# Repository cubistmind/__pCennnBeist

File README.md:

# ___being_pCB-eist
welcome to tHe world of my own custom pcB's

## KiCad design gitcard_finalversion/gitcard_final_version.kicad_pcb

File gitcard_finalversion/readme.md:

# PCB gitcard -stuckatprototype

A custom PCB based "emniii😞😞" card that lets you play a version of Flappy Bird

## Project Structure
The project consists of
1. Firmware
2. Hardware
3. Mechanical
4. Scripts

These are structured into their own files. I could have used submodules, but decided against it.

### 1. Firmware
This lives on the ESP32
soon the necessary firmware files will be included here 
### 2. Hardware

#### Schematic
PDF schematic included for your viewing pleasure.
#### PCBs
All the gerber files you'd need to send to a fab house.
#### Kicad
All the files you'd need to expand and work on this further. If you'd like.

### 3. Mechanical

#### Enclosure
All the step files you need to make one of these. Extrusion printer works well for this part.

### 4. Scripts

soon it will be added🥲

#### Requirements
A bunch of pip packages

## What the project could use
1. Cleanup, but thats true for almost anything out there
2. A proper graphics library -- Adafruit, or even LVGL 
3. Scripts that would show stock data. anyone? 

## If you take it further
Let me know if you ever make one of these, I'd love to see it. Seriously, that'd be exciting and inspiring to keep making my projects open source!

## Known issues
1. Switch requires to be shorted due to power consumption at run time
2. GPIO 1 as is does not allow the device to wake up from sleep
3. The LEDs seem to be pulling a lot power even when ESP32 is in deep sleep mode
## Special Thanks
Thanks to Michael Angerer for his open sourced `esp32_ble_ota` project. I used it to get BLE running in this project. His blog post and github repo are a great resource. Check it out. https://github.com/micha

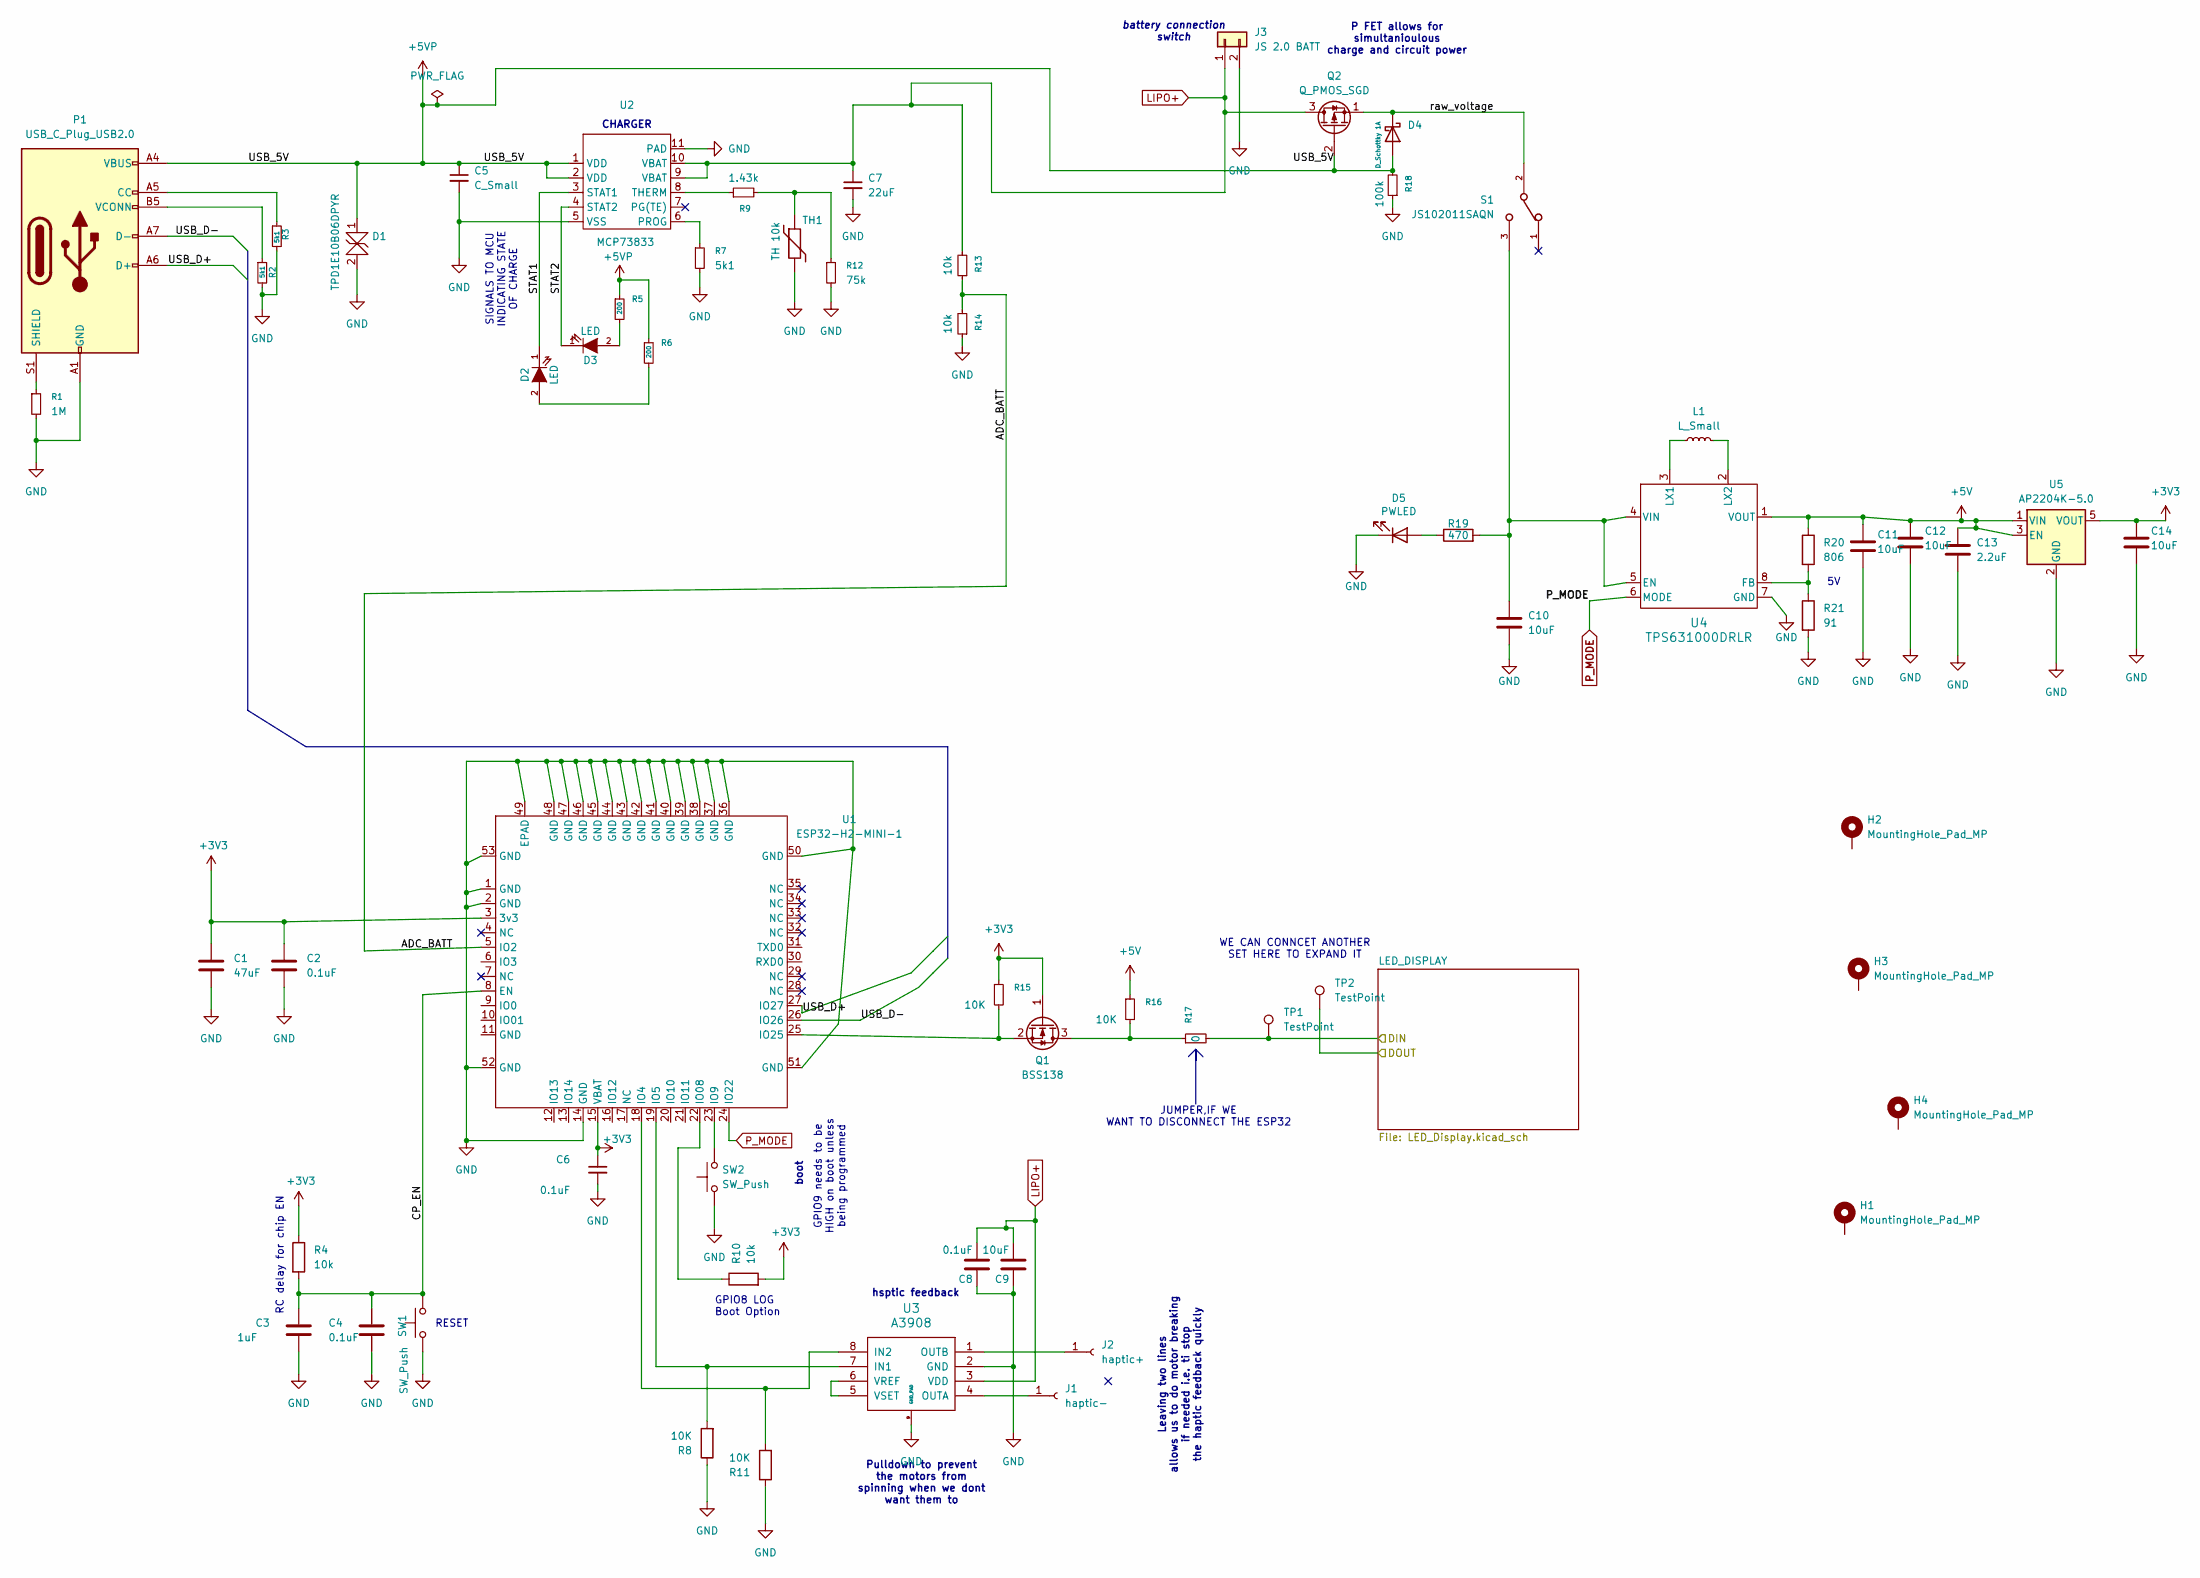
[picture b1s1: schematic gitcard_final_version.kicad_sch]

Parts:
C1: 47uF; C_0603_1608Metric
C2, C4, C6, C8: 0.1uF; C_0603_1608Metric
C3: 1uF; C_0603_1608Metric
C5: C_Small; C_0603_1608Metric
C7: 22uF; C_0603_1608Metric
C9, C10, C11, C12, C14: 10uF; C_0603_1608Metric
C13: 2.2uF; C_0603_1608Metric
D1: TPD1E10B06DPYR; D_SOD-523
D2, D3: LED; D_0603_1608Metric
D4: D_Schottky 1A; D_SMA
D5: PWLED; D_0603_1608Metric
H1, H2, H3, H4: MountingHole_Pad_MP; MountingHole_3.5mm_Pad_TopBottom
J1: haptic-; SolderWirePad_1x01_SMD_3x6mm
J2: haptic+; SolderWirePad_1x01_SMD_3x6mm
J3: JS 2.0 BATT; JST_PH_B2B-PH-SM4-TB_1x02-1MP_P2.00mm_Vertical
L1: L_Small; L_0805_2012Metric
P1: USB_C_Plug_USB2.0; USB_C_Plug_Molex_105444
Q1: BSS138; SOT-23
Q2: Q_PMOS_SGD; SOT-89-3
R1: 1M; L_0805_2012Metric
R2, R3, R7: 5k1; R_0603_1608Metric
R4, R10, R13, R14: 10k; R_0603_1608Metric
R5, R6: 200; R_0603_1608Metric
R8, R11, R15, R16: 10K; R_0603_1608Metric
R9: 1.43k; R_0603_1608Metric
R12: 75k; R_0603_1608Metric
R17: 0; R_0603_1608Metric
R18: 100k; R_0603_1608Metric
R19: 470; R_0603_1608Metric
R20: 806; R_0603_1608Metric
R21: 91; R_0603_1608Metric
S1: JS102011SAQN; SW_SPDT_CK_JS102011SAQN
SW1, SW2: SW_Push; SW_Push_1P1T_NO_CK_KSC7xxJ
TH1: TH 10k; R_0603_1608Metric
TP1, TP2: TestPoint; TestPoint_Pad_1.5x1.5mm
U1: ESP32-H2-MINI-1; MODULE_ESP32-H2-MINI-1-H2_1
U2: MCP73833; SON50P300X300X100-11N
U3: A3908
U4: TPS631000DRLR; TPS631000DRLR_TEX
U5: AP2204K-5.0; SOT-23-5

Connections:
+3V3: C1.1, C2.1, C6.1, C14.1, Q1.1 (G), R4.1, R10.2, R15.1, U1.3 (3v3), U1.15 (VBAT), U5.5 (VOUT)
+5V: C11.1, C12.1, C13.1, R16.1, R20.1, U4.1 (VOUT), U5.1 (VIN), U5.3 (EN); also elsewhere on the board
+5VP: C5.1, D1.1, D4.2 (A), P1.A4 (VBUS), P1.A9 (VBUS), P1.B4 (VBUS), P1.B9 (VBUS), Q2.2 (G), R5.1, R6.1, R18.2, U2.1 (VDD), U2.2 (VDD)
/ADC_BATT: R13.1, R14.2, U1.5 (IO2)
/CP_EN: C3.1, C4.1, R4.2, SW1.2, U1.8 (EN)
/DIN: R17.2, TP1.1 (1_1)
/DOUT: TP2.1 (1_1)
/STAT1: D2.1 (K), U2.3 (STAT1)
/STAT2: D3.1 (K), U2.4 (STAT2)
/USB_D+: P1.A6 (D+), U1.27 (IO27)
/USB_D-: P1.A7 (D-), U1.26 (IO26)
/raw_voltage: D4.1 (K), Q2.1 (S), S1.2
GND: C1.2, C2.2, C3.2, C4.2, C5.2, C6.2, C7.2, C8.1, C9.1, C10.2, C11.2, C12.2, C13.2, C14.2, D1.2, D5.1 (K), J3.2, P1.A1 (GND), P1.A12 (GND), P1.B1 (GND), P1.B12 (GND), R1.2, R2.2, R3.2, R7.2, R8.1, R11.1, R12.2, R14.1, R18.1, R21.2, SW1.1, SW2.1, TH1.2, U1.1 (GND), U1.2 (GND), U1.14 (GND), U1.36 (GND), U1.37 (GND), U1.38 (GND), U1.39 (GND), U1.40 (GND), U1.41 (GND), U1.42 (GND), U1.43 (GND), U1.44 (GND), U1.45 (GND), U1.46 (GND), U1.47 (GND), U1.48 (GND), U1.49 (EPAD), U1.50 (GND), U1.51 (GND), U1.52 (GND), U1.53 (GND), U2.5 (VSS), U2.11 (PAD), U3.2 (GND), U3.9 (GND_PAD), U4.7 (GND), U5.2 (GND); also elsewhere on the board
LIPO+: C7.1, C8.2, C9.2, J3.1, Q2.3 (D), R13.2, U2.9 (VBAT), U2.10 (VBAT), U3.3 (VDD)
unnamed: D2.2 (A), R6.2
unnamed: D3.2 (A), R5.2
unnamed: D5.2 (A), R19.1
unnamed: J1.1 (Pin_1_1), U3.4 (OUTA)
unnamed: J2.1 (Pin_1_1), U3.1 (OUTB)
unnamed: P1.A5 (CC), R3.1
unnamed: P1.S1 (SHIELD), R1.1
unnamed: P1.B5 (VCONN), R2.1
unnamed: Q1.3 (D), R16.2, R17.1
unnamed: Q1.2 (S), R15.2, U1.25 (IO25)
unnamed: R9.2, R12.1, TH1.1
unnamed: R11.2, U1.18 (IO4), U3.8 (IN2)
unnamed: R8.2, U1.19 (IO5), U3.7 (IN1)
unnamed: R10.1, U1.22 (IO08)
unnamed: SW2.2, U1.23 (IO9)
unnamed: R7.1, U2.6 (PROG)
unnamed: R9.1, U2.8 (THERM)
unnamed: U3.5 (VSET), U3.6 (VREF)
unnamed: C10.1, R19.2, S1.3, U4.4 (VIN), U4.5 (EN)
unnamed: R20.2, R21.1, U4.8 (FB)
unnamed: L1.1, U4.3 (LX1)
unnamed: L1.2, U4.2 (LX2)
P_MODE: U1.24 (IO22), U4.6 (MODE)

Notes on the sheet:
battery connection switch
Pulldown to prevent the motors from spinning when we dont want them to
boot
CHARGER
RESET
SIGNALS TO MCU INDICATING STATE OF CHARGE
Leaving two lines allows us to do motor breaking if needed i.e. ti stop the haptic feedback quickly
JUMPER,IF WE WANT TO DISCONNECT THE ESP32
GPIO9 needs to be HIGH on boot unless being programmed
GPIO8 LOG Boot Option
WE CAN CONNCET ANOTHER SET HERE TO EXPAND IT
P FET allows for simultanioulous charge and circuit power
RC delay for chip EN
hsptic feedback

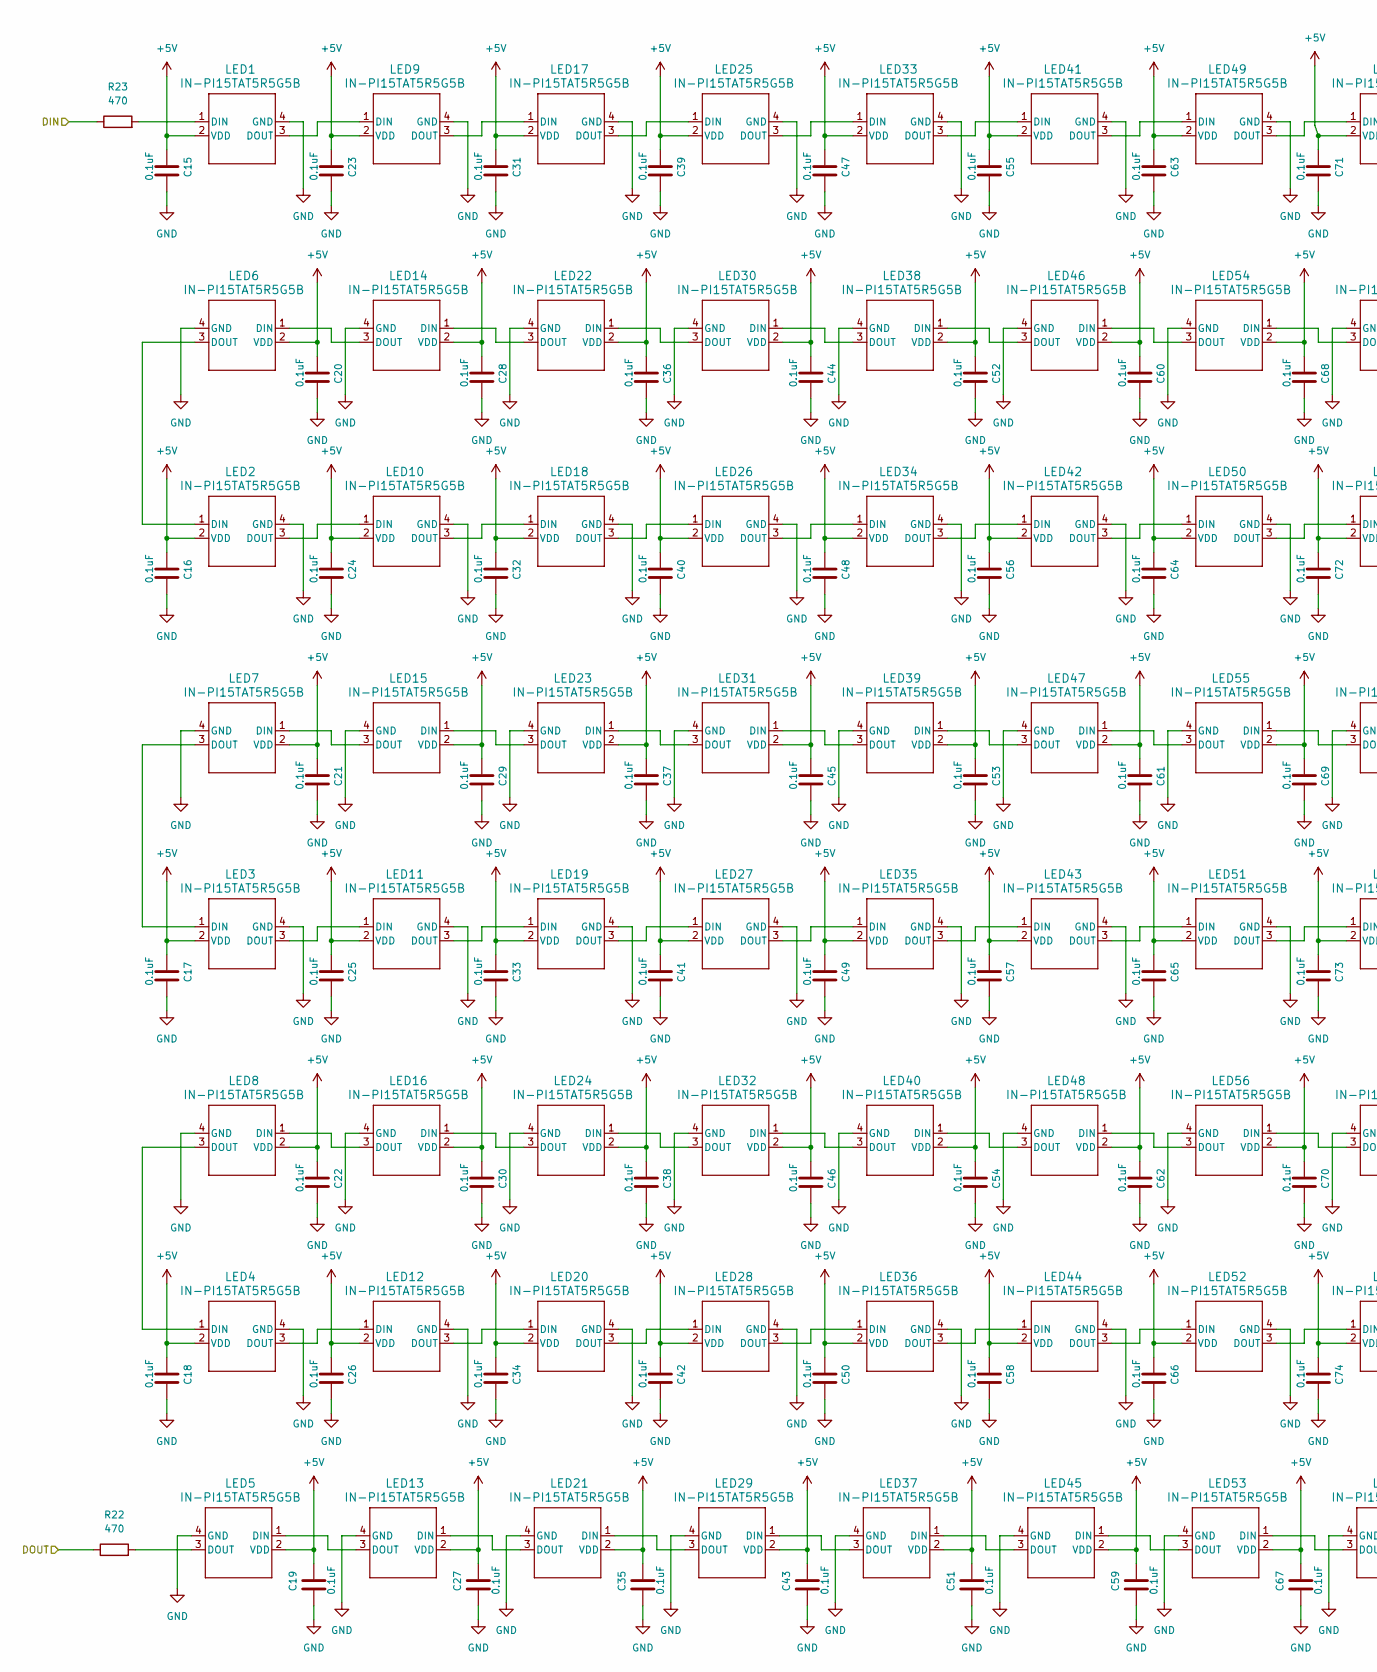
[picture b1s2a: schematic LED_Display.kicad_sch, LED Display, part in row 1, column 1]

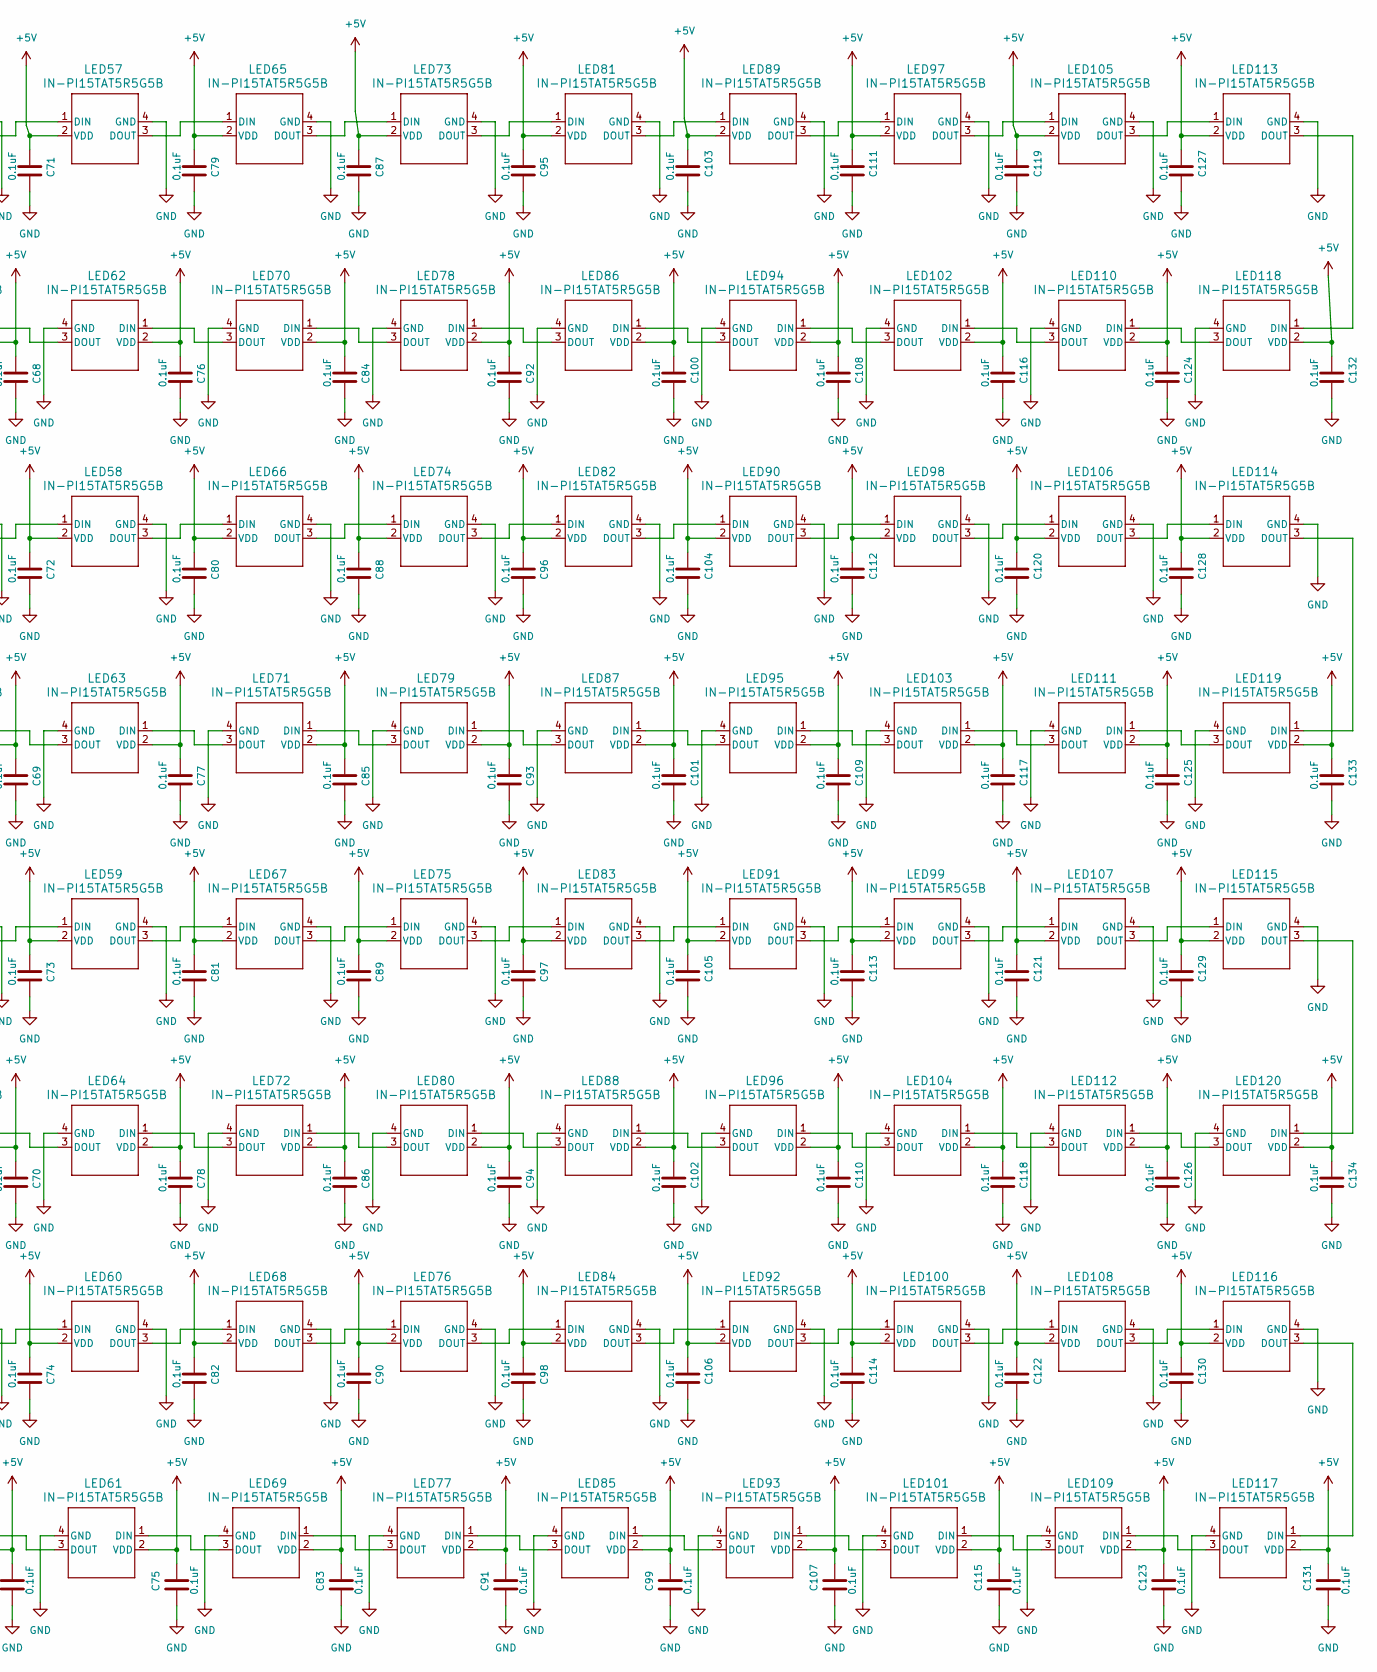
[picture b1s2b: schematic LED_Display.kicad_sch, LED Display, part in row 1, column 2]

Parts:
C15, C16, C17, C18, C19, C20, C21, C22, C23, C24, C25, C26, C27, C28, C29, C30, C31, C32, C33, C34, C35, C36, C37, C38, C39, C40, C41, C42, C43, C44, C45, C46, C47, C48, C49, C50, C51, C52, C53, C54, C55, C56, C57, C58, C59, C60, C61, C62, C63, C64, C65, C66, C67, C68, C69, C70, C71, C72, C73, C74, C75, C76, C77, C78, C79, C80, C81, C82, C83, C84, C85, C86, C87, C88, C89, C90, C91, C92, C93, C94, C95, C96, C97, C98, C99, C100, C101, C102, C103, C104, C105, C106, C107, C108, C109, C110, C111, C112, C113, C114, C115, C116, C117, C118, C119, C120, C121, C122, C123, C124, C125, C126, C127, C128, C129, C130, C131, C132, C133, C134: 0.1uF; C_0603_1608Metric
LED1, LED2, LED3, LED4, LED5, LED6, LED7, LED8, LED9, LED10, LED11, LED12, LED13, LED14, LED15, LED16, LED17, LED18, LED19, LED20, LED21, LED22, LED23, LED24, LED25, LED26, LED27, LED28, LED29, LED30, LED31, LED32, LED33, LED34, LED35, LED36, LED37, LED38, LED39, LED40, LED41, LED42, LED43, LED44, LED45, LED46, LED47, LED48, LED49, LED50, LED51, LED52, LED53, LED54, LED55, LED56, LED57, LED58, LED59, LED60, LED61, LED62, LED63, LED64, LED65, LED66, LED67, LED68, LED69, LED70, LED71, LED72, LED73, LED74, LED75, LED76, LED77, LED78, LED79, LED80, LED81, LED82, LED83, LED84, LED85, LED86, LED87, LED88, LED89, LED90, LED91, LED92, LED93, LED94, LED95, LED96, LED97, LED98, LED99, LED100, LED101, LED102, LED103, LED104, LED105, LED106, LED107, LED108, LED109, LED110, LED111, LED112, LED113, LED114, LED115, LED116, LED117, LED118, LED119, LED120: IN-PI15TAT5R5G5B; IN-PI15_INL
R22, R23: 470; R_0603_1608Metric

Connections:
+5V: C15.1, C16.1, C17.1, C18.1, C19.1, C20.1, C21.1, C22.1, C23.1, C24.1, C25.1, C26.1, C27.1, C28.1, C29.1, C30.1, C31.1, C32.1, C33.1, C34.1, C35.1, C36.1, C37.1, C38.1, C39.1, C40.1, C41.1, C42.1, C43.1, C44.1, C45.1, C46.1, C47.1, C48.1, C49.1, C50.1, C51.1, C52.1, C53.1, C54.1, C55.1, C56.1, C57.1, C58.1, C59.1, C60.1, C61.1, C62.1, C63.1, C64.1, C65.1, C66.1, C67.1, C68.1, C69.1, C70.1, C71.1, C72.1, C73.1, C74.1, C75.1, C76.1, C77.1, C78.1, C79.1, C80.1, C81.1, C82.1, C83.1, C84.1, C85.1, C86.1, C87.1, C88.1, C89.1, C90.1, C91.1, C92.1, C93.1, C94.1, C95.1, C96.1, C97.1, C98.1, C99.1, C100.1, C101.1, C102.1, C103.1, C104.1, C105.1, C106.1, C107.1, C108.1, C109.1, C110.1, C111.1, C112.1, C113.1, C114.1, C115.1, C116.1, C117.1, C118.1, C119.1, C120.1, C121.1, C122.1, C123.1, C124.1, C125.1, C126.1, C127.1, C128.1, C129.1, C130.1, C131.1, C132.1, C133.1, C134.1, LED1.2 (VDD), LED2.2 (VDD), LED3.2 (VDD), LED4.2 (VDD), LED5.2 (VDD), LED6.2 (VDD), LED7.2 (VDD), LED8.2 (VDD), LED9.2 (VDD), LED10.2 (VDD), LED11.2 (VDD), LED12.2 (VDD), LED13.2 (VDD), LED14.2 (VDD), LED15.2 (VDD), LED16.2 (VDD), LED17.2 (VDD), LED18.2 (VDD), LED19.2 (VDD), LED20.2 (VDD), LED21.2 (VDD), LED22.2 (VDD), LED23.2 (VDD), LED24.2 (VDD), LED25.2 (VDD), LED26.2 (VDD), LED27.2 (VDD), LED28.2 (VDD), LED29.2 (VDD), LED30.2 (VDD), LED31.2 (VDD), LED32.2 (VDD), LED33.2 (VDD), LED34.2 (VDD), LED35.2 (VDD), LED36.2 (VDD), LED37.2 (VDD), LED38.2 (VDD), LED39.2 (VDD), LED40.2 (VDD), LED41.2 (VDD), LED42.2 (VDD), LED43.2 (VDD), LED44.2 (VDD), LED45.2 (VDD), LED46.2 (VDD), LED47.2 (VDD)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; also elsewhere on the board
/LED_DISPLAY/DIN: R23.1
/LED_DISPLAY/DOUT: R22.1
GND: C15.2, C16.2, C17.2, C18.2, C19.2, C20.2, C21.2, C22.2, C23.2, C24.2, C25.2, C26.2, C27.2, C28.2, C29.2, C30.2, C31.2, C32.2, C33.2, C34.2, C35.2, C36.2, C37.2, C38.2, C39.2, C40.2, C41.2, C42.2, C43.2, C44.2, C45.2, C46.2, C47.2, C48.2, C49.2, C50.2, C51.2, C52.2, C53.2, C54.2, C55.2, C56.2, C57.2, C58.2, C59.2, C60.2, C61.2, C62.2, C63.2, C64.2, C65.2, C66.2, C67.2, C68.2, C69.2, C70.2, C71.2, C72.2, C73.2, C74.2, C75.2, C76.2, C77.2, C78.2, C79.2, C80.2, C81.2, C82.2, C83.2, C84.2, C85.2, C86.2, C87.2, C88.2, C89.2, C90.2, C91.2, C92.2, C93.2, C94.2, C95.2, C96.2, C97.2, C98.2, C99.2, C100.2, C101.2, C102.2, C103.2, C104.2, C105.2, C106.2, C107.2, C108.2, C109.2, C110.2, C111.2, C112.2, C113.2, C114.2, C115.2, C116.2, C117.2, C118.2, C119.2, C120.2, C121.2, C122.2, C123.2, C124.2, C125.2, C126.2, C127.2, C128.2, C129.2, C130.2, C131.2, C132.2, C133.2, C134.2, LED1.4 (GND), LED2.4 (GND), LED3.4 (GND), LED4.4 (GND), LED5.4 (GND), LED6.4 (GND), LED7.4 (GND), LED8.4 (GND), LED9.4 (GND), LED10.4 (GND), LED11.4 (GND), LED12.4 (GND), LED13.4 (GND), LED14.4 (GND), LED15.4 (GND), LED16.4 (GND), LED17.4 (GND), LED18.4 (GND), LED19.4 (GND), LED20.4 (GND), LED21.4 (GND), LED22.4 (GND), LED23.4 (GND), LED24.4 (GND), LED25.4 (GND), LED26.4 (GND), LED27.4 (GND), LED28.4 (GND), LED29.4 (GND), LED30.4 (GND), LED31.4 (GND), LED32.4 (GND), LED33.4 (GND), LED34.4 (GND), LED35.4 (GND), LED36.4 (GND), LED37.4 (GND), LED38.4 (GND), LED39.4 (GND), LED40.4 (GND), LED41.4 (GND), LED42.4 (GND), LED43.4 (GND), LED44.4 (GND), LED45.4 (GND), LED46.4 (GND), LED47.4 (GND)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; also elsewhere on the board
unnamed: LED1.1 (DIN), R23.2
unnamed: LED1.3 (DOUT), LED9.1 (DIN)
unnamed: LED2.1 (DIN), LED6.3 (DOUT)
unnamed: LED3.1 (DIN), LED7.3 (DOUT)
unnamed: LED4.1 (DIN), LED8.3 (DOUT)
unnamed: LED5.3 (DOUT), R22.2
unnamed: LED2.3 (DOUT), LED10.1 (DIN)
unnamed: LED10.3 (DOUT), LED18.1 (DIN)
unnamed: LED3.3 (DOUT), LED11.1 (DIN)
unnamed: LED11.3 (DOUT), LED19.1 (DIN)
unnamed: LED4.3 (DOUT), LED12.1 (DIN)
unnamed: LED12.3 (DOUT), LED20.1 (DIN)
unnamed: LED13.1 (DIN), LED21.3 (DOUT)
unnamed: LED5.1 (DIN), LED13.3 (DOUT)
unnamed: LED14.1 (DIN), LED22.3 (DOUT)
unnamed: LED6.1 (DIN), LED14.3 (DOUT)
unnamed: LED15.1 (DIN), LED23.3 (DOUT)
unnamed: LED7.1 (DIN), LED15.3 (DOUT)
unnamed: LED16.1 (DIN), LED24.3 (DOUT)
unnamed: LED8.1 (DIN), LED16.3 (DOUT)
unnamed: LED9.3 (DOUT), LED17.1 (DIN)
unnamed: LED17.3 (DOUT), LED25.1 (DIN)
unnamed: LED18.3 (DOUT), LED26.1 (DIN)
unnamed: LED19.3 (DOUT), LED27.1 (DIN)
unnamed: LED20.3 (DOUT), LED28.1 (DIN)
unnamed: LED21.1 (DIN), LED29.3 (DOUT)
unnamed: LED22.1 (DIN), LED30.3 (DOUT)
unnamed: LED23.1 (DIN), LED31.3 (DOUT)
unnamed: LED24.1 (DIN), LED32.3 (DOUT)
unnamed: LED25.3 (DOUT), LED33.1 (DIN)
unnamed: LED26.3 (DOUT), LED34.1 (DIN)
unnamed: LED27.3 (DOUT), LED35.1 (DIN)
unnamed: LED28.3 (DOUT), LED36.1 (DIN)
unnamed: LED29.1 (DIN), LED37.3 (DOUT)
unnamed: LED30.1 (DIN), LED38.3 (DOUT)
unnamed: LED31.1 (DIN), LED39.3 (DOUT)
unnamed: LED32.1 (DIN), LED40.3 (DOUT)
unnamed: LED33.3 (DOUT), LED41.1 (DIN)
unnamed: LED34.3 (DOUT), LED42.1 (DIN)
unnamed: LED35.3 (DOUT), LED43.1 (DIN)
unnamed: LED36.3 (DOUT), LED44.1 (DIN)
unnamed: LED37.1 (DIN), LED45.3 (DOUT)
unnamed: LED38.1 (DIN), LED46.3 (DOUT)
unnamed: LED39.1 (DIN), LED47.3 (DOUT)
unnamed: LED40.1 (DIN), LED48.3 (DOUT)
unnamed: LED41.3 (DOUT), LED49.1 (DIN)
unnamed: LED42.3 (DOUT), LED50.1 (DIN)
unnamed: LED43.3 (DOUT), LED51.1 (DIN)
unnamed: LED44.3 (DOUT), LED52.1 (DIN)
unnamed: LED45.1 (DIN), LED53.3 (DOUT)
unnamed: LED46.1 (DIN), LED54.3 (DOUT)
unnamed: LED47.1 (DIN), LED55.3 (DOUT)
unnamed: LED48.1 (DIN), LED56.3 (DOUT)
unnamed: LED49.3 (DOUT), LED57.1 (DIN)
unnamed: LED50.3 (DOUT), LED58.1 (DIN)
unnamed: LED51.3 (DOUT), LED59.1 (DIN)
unnamed: LED52.3 (DOUT), LED60.1 (DIN)
unnamed: LED53.1 (DIN), LED61.3 (DOUT)
unnamed: LED54.1 (DIN), LED62.3 (DOUT)
unnamed: LED55.1 (DIN), LED63.3 (DOUT)
unnamed: LED56.1 (DIN), LED64.3 (DOUT)
unnamed: LED57.3 (DOUT), LED65.1 (DIN)
unnamed: LED58.3 (DOUT), LED66.1 (DIN)
unnamed: LED59.3 (DOUT), LED67.1 (DIN)
unnamed: LED60.3 (DOUT), LED68.1 (DIN)
unnamed: LED61.1 (DIN), LED69.3 (DOUT)
unnamed: LED62.1 (DIN), LED70.3 (DOUT)
unnamed: LED63.1 (DIN), LED71.3 (DOUT)
unnamed: LED64.1 (DIN), LED72.3 (DOUT)
unnamed: LED65.3 (DOUT), LED73.1 (DIN)
unnamed: LED66.3 (DOUT), LED74.1 (DIN)
unnamed: LED67.3 (DOUT), LED75.1 (DIN)
unnamed: LED68.3 (DOUT), LED76.1 (DIN)
unnamed: LED69.1 (DIN), LED77.3 (DOUT)
unnamed: LED70.1 (DIN), LED78.3 (DOUT)
unnamed: LED71.1 (DIN), LED79.3 (DOUT)
unnamed: LED72.1 (DIN), LED80.3 (DOUT)
unnamed: LED73.3 (DOUT), LED81.1 (DIN)
unnamed: LED74.3 (DOUT), LED82.1 (DIN)
unnamed: LED75.3 (DOUT), LED83.1 (DIN)
unnamed: LED76.3 (DOUT), LED84.1 (DIN)
unnamed: LED77.1 (DIN), LED85.3 (DOUT)
unnamed: LED78.1 (DIN), LED86.3 (DOUT)
unnamed: LED79.1 (DIN), LED87.3 (DOUT)
unnamed: LED80.1 (DIN), LED88.3 (DOUT)
unnamed: LED81.3 (DOUT), LED89.1 (DIN)
unnamed: LED82.3 (DOUT), LED90.1 (DIN)
unnamed: LED83.3 (DOUT), LED91.1 (DIN)
unnamed: LED84.3 (DOUT), LED92.1 (DIN)
unnamed: LED85.1 (DIN), LED93.3 (DOUT)
unnamed: LED86.1 (DIN), LED94.3 (DOUT)
unnamed: LED87.1 (DIN), LED95.3 (DOUT)
unnamed: LED88.1 (DIN), LED96.3 (DOUT)
unnamed: LED89.3 (DOUT), LED97.1 (DIN)
unnamed: LED90.3 (DOUT), LED98.1 (DIN)
unnamed: LED91.3 (DOUT), LED99.1 (DIN)
unnamed: LED92.3 (DOUT), LED100.1 (DIN)
unnamed: LED100.3 (DOUT), LED108.1 (DIN)
unnamed: LED101.1 (DIN), LED109.3 (DOUT)
unnamed: LED93.1 (DIN), LED101.3 (DOUT)
unnamed: LED102.1 (DIN), LED110.3 (DOUT)
unnamed: LED94.1 (DIN), LED102.3 (DOUT)
unnamed: LED103.1 (DIN), LED111.3 (DOUT)
unnamed: LED95.1 (DIN), LED103.3 (DOUT)
unnamed: LED104.1 (DIN), LED112.3 (DOUT)
unnamed: LED96.1 (DIN), LED104.3 (DOUT)
unnamed: LED97.3 (DOUT), LED105.1 (DIN)
unnamed: LED105.3 (DOUT), LED113.1 (DIN)
unnamed: LED98.3 (DOUT), LED106.1 (DIN)
unnamed: LED106.3 (DOUT), LED114.1 (DIN)
unnamed: LED99.3 (DOUT), LED107.1 (DIN)
unnamed: LED107.3 (DOUT), LED115.1 (DIN)
unnamed: LED108.3 (DOUT), LED116.1 (DIN)
unnamed: LED109.1 (DIN), LED117.3 (DOUT)
unnamed: LED110.1 (DIN), LED118.3 (DOUT)
unnamed: LED111.1 (DIN), LED119.3 (DOUT)
unnamed: LED112.1 (DIN), LED120.3 (DOUT)
unnamed: LED113.3 (DOUT), LED118.1 (DIN)
unnamed: LED114.3 (DOUT), LED119.1 (DIN)
unnamed: LED115.3 (DOUT), LED120.1 (DIN)
unnamed: LED116.3 (DOUT), LED117.1 (DIN)

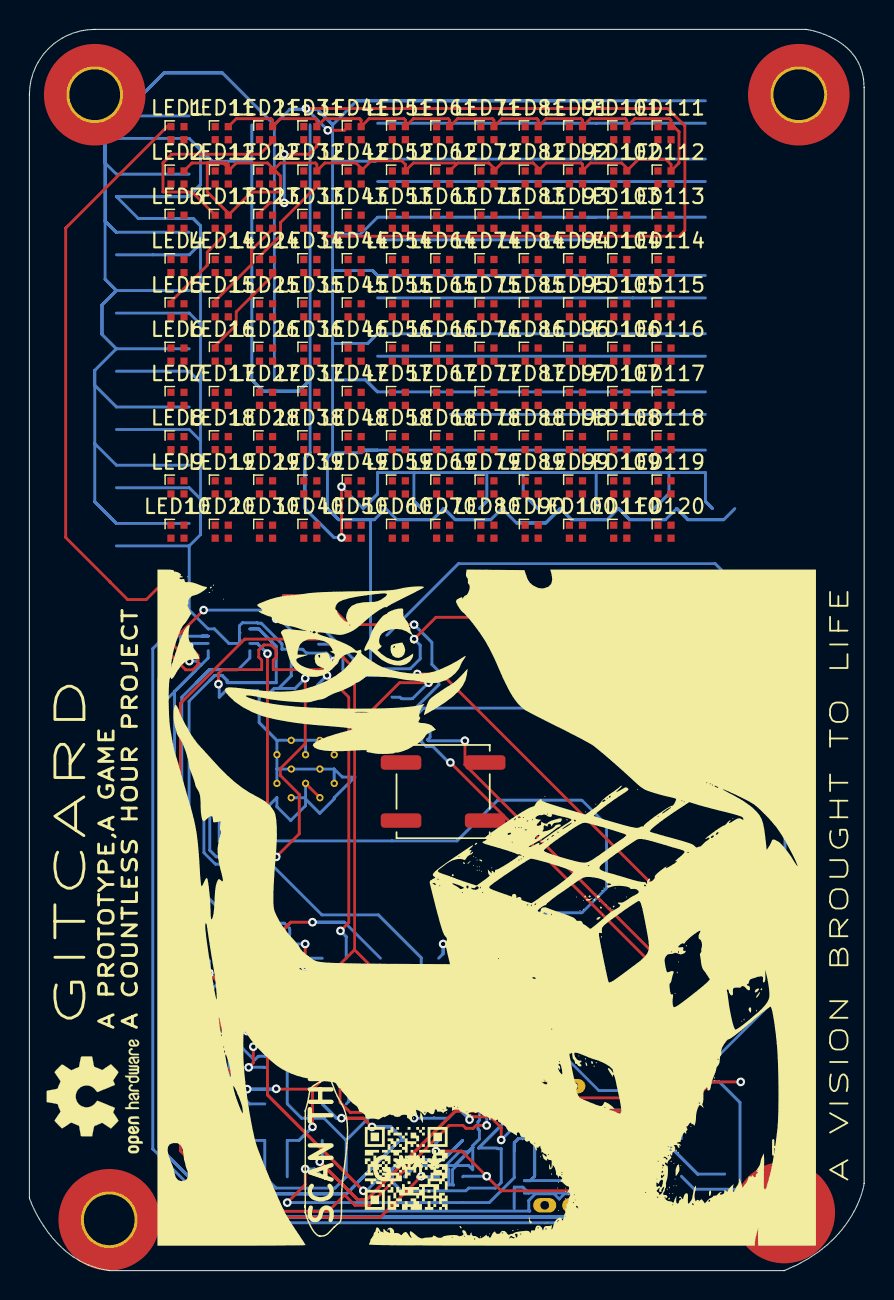
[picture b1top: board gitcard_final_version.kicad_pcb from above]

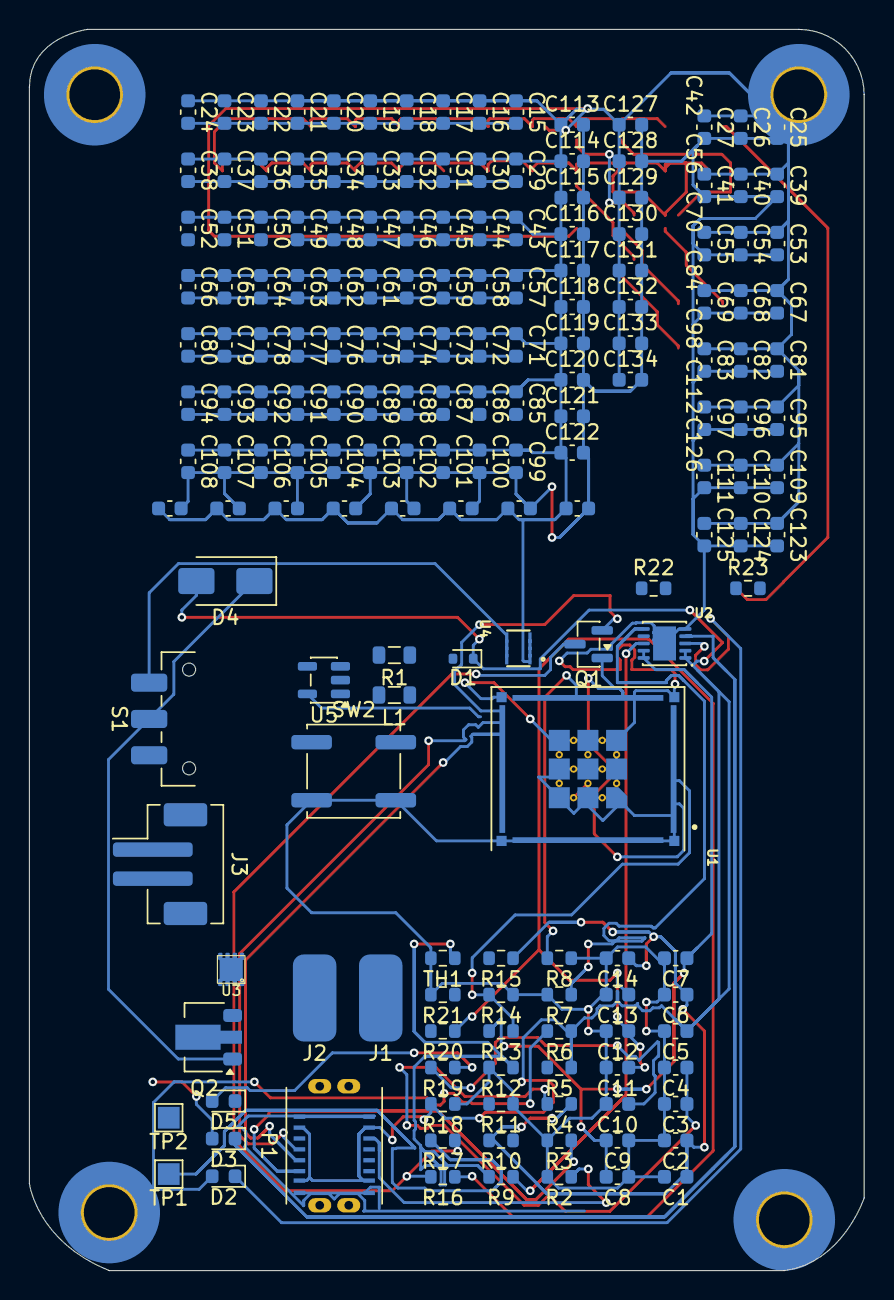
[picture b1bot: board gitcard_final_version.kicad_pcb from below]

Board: 2 copper layers, 57.5 x 85.5 mm, 304 parts (179 on the bottom side), 156 nets.

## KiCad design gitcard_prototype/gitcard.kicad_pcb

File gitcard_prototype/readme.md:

# GITCARD PROTOTYPE🥲🤦‍♀️🙄
https://github.com/user-attachments/assets/325de9ae-36e4-4504-b71e-95f378eeccd0

This is the commencement of the gitcard project 
asap it will be transformed to the actual project

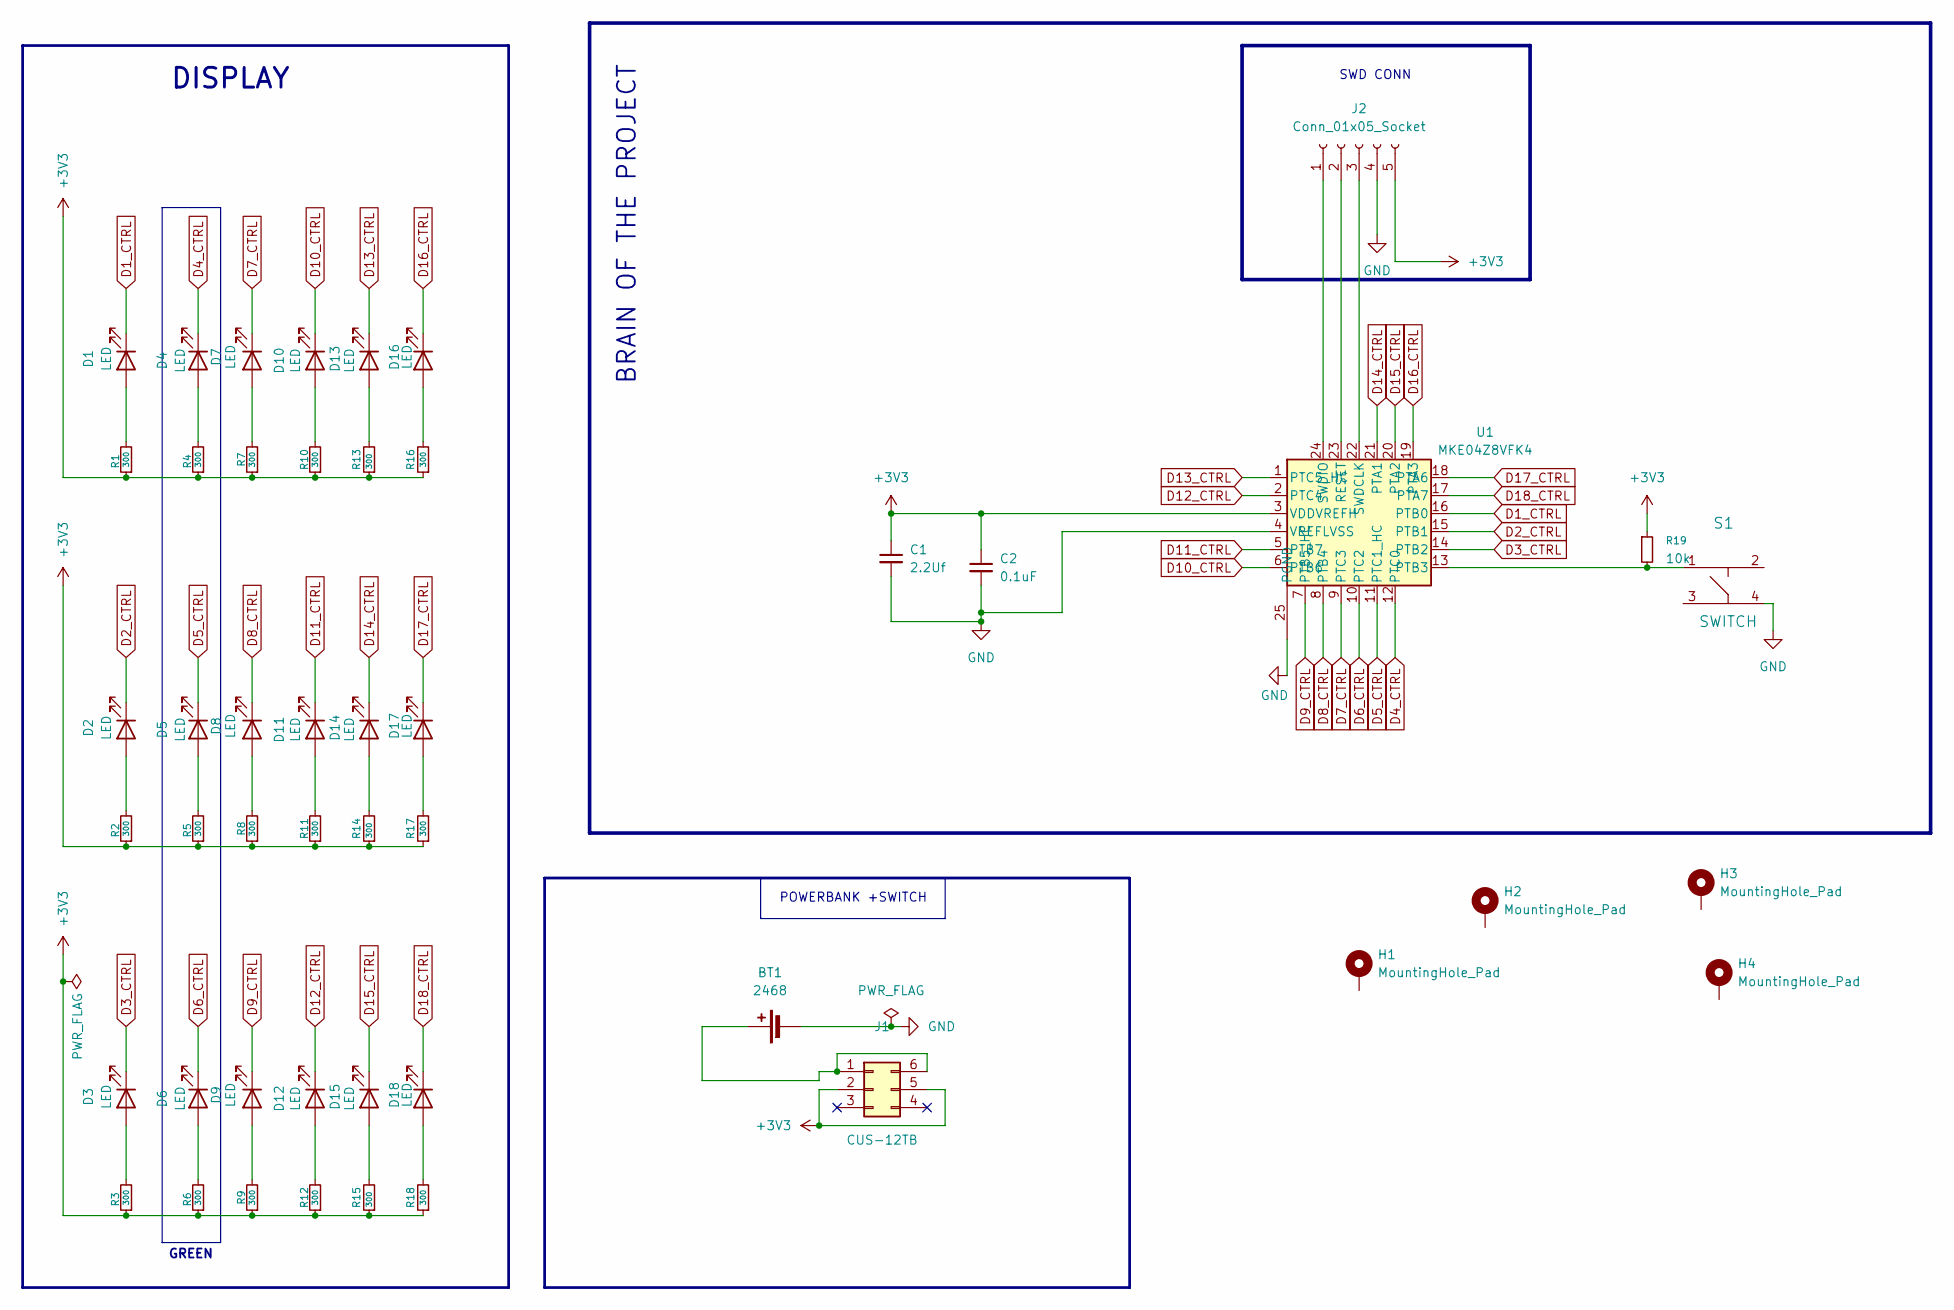
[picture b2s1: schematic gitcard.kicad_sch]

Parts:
BT1: 2468; BatteryHolder_MPD_BA9VPC_1xPP3
C1: 2.2Uf; C_0603_1608Metric
C2: 0.1uF; C_0603_1608Metric
D1, D2, D3, D4, D5, D6, D7, D8, D9, D10, D11, D12, D13, D14, D15, D16, D17, D18: LED; LED_0603_1608Metric
H1, H2, H3, H4: MountingHole_Pad; MountingHole_2.2mm_M2_ISO7380_Pad_TopBottom
J1: CUS-12TB
J2: Conn_01x05_Socket; PinHeader_1x05_P1.27mm_Vertical
R1, R2, R3, R4, R5, R6, R7, R8, R9, R10, R11, R12, R13, R14, R15, R16, R17, R18: 300; R_0603_1608Metric
R19: 10k; R_0603_1608Metric
S1: SWITCH; PTS645SM43SMTR92
U1: MKE04Z8VFK4

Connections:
+3V3: C1.1, C2.1, J1.2, J1.5, J2.5, R1.1, R2.1, R3.1, R4.1, R5.1, R6.1, R7.1, R8.1, R9.1, R10.1, R11.1, R12.1, R13.1, R14.1, R15.1, R16.1, R17.1, R18.1, R19.1, U1.3 (VDDVREFH)
D1_CTRL: D1.1 (K), U1.16 (PTB0)
D2_CTRL: D2.1 (K), U1.15 (PTB1)
D3_CTRL: D3.1 (K), U1.14 (PTB2)
D4_CTRL: D4.1 (K), U1.12 (PTC0)
D5_CTRL: D5.1 (K), U1.11 (PTC1_HC)
D6_CTRL: D6.1 (K), U1.10 (PTC2)
D7_CTRL: D7.1 (K), U1.9 (PTC3)
D8_CTRL: D8.1 (K), U1.8 (PTB4)
D9_CTRL: D9.1 (K), U1.7 (PTB5_HC)
D10_CTRL: D10.1 (K), U1.6 (PTB6)
D11_CTRL: D11.1 (K), U1.5 (PTB7)
D12_CTRL: D12.1 (K), U1.2 (PTC4)
D13_CTRL: D13.1 (K), U1.1 (PTC5_HC)
D14_CTRL: D14.1 (K), U1.21 (PTA1)
D15_CTRL: D15.1 (K), U1.20 (PTA2)
D16_CTRL: D16.1 (K), U1.19 (PTA3)
D17_CTRL: D17.1 (K), U1.18 (PTA6)
D18_CTRL: D18.1 (K), U1.17 (PTA7)
GND: BT1.2 (-), C1.2, C2.2, J2.4, S1.4, U1.4 (VREFLVSS), U1.25 (PGND)
unnamed: BT1.1 (+), J1.1, J1.6
unnamed: D1.2 (A), R1.2
unnamed: D2.2 (A), R2.2
unnamed: D3.2 (A), R3.2
unnamed: D4.2 (A), R4.2
unnamed: D5.2 (A), R5.2
unnamed: D6.2 (A), R6.2
unnamed: D7.2 (A), R7.2
unnamed: D8.2 (A), R8.2
unnamed: D9.2 (A), R9.2
unnamed: D10.2 (A), R10.2
unnamed: D11.2 (A), R11.2
unnamed: D12.2 (A), R12.2
unnamed: D13.2 (A), R13.2
unnamed: D14.2 (A), R14.2
unnamed: D15.2 (A), R15.2
unnamed: D16.2 (A), R16.2
unnamed: D17.2 (A), R17.2
unnamed: D18.2 (A), R18.2
unnamed: J2.1, U1.24 (SWDIO)
unnamed: J2.2, U1.23 (RESET)
unnamed: J2.3, U1.22 (SWDCLK)
unnamed: R19.2, S1.1, U1.13 (PTB3)

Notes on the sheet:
BRAIN OF THE PROJECT
POWERBANK +SWITCH
DISPLAY
SWD CONN
GREEN

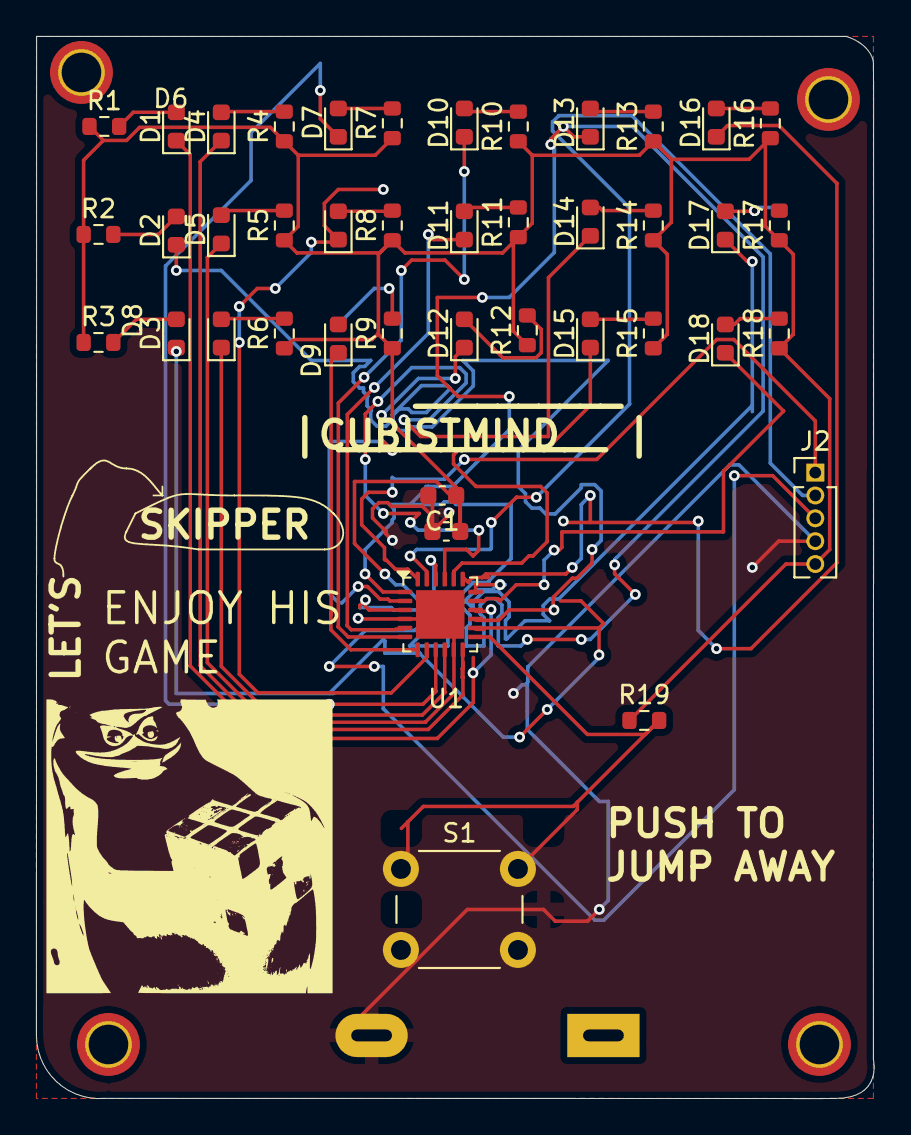
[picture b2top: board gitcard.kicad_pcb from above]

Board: 2 copper layers, 46.5 x 59.0 mm, 47 parts (1 on the bottom side), 42 nets.
